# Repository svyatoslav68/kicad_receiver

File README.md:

Схема и печатная плата для FM-радиоприемника.

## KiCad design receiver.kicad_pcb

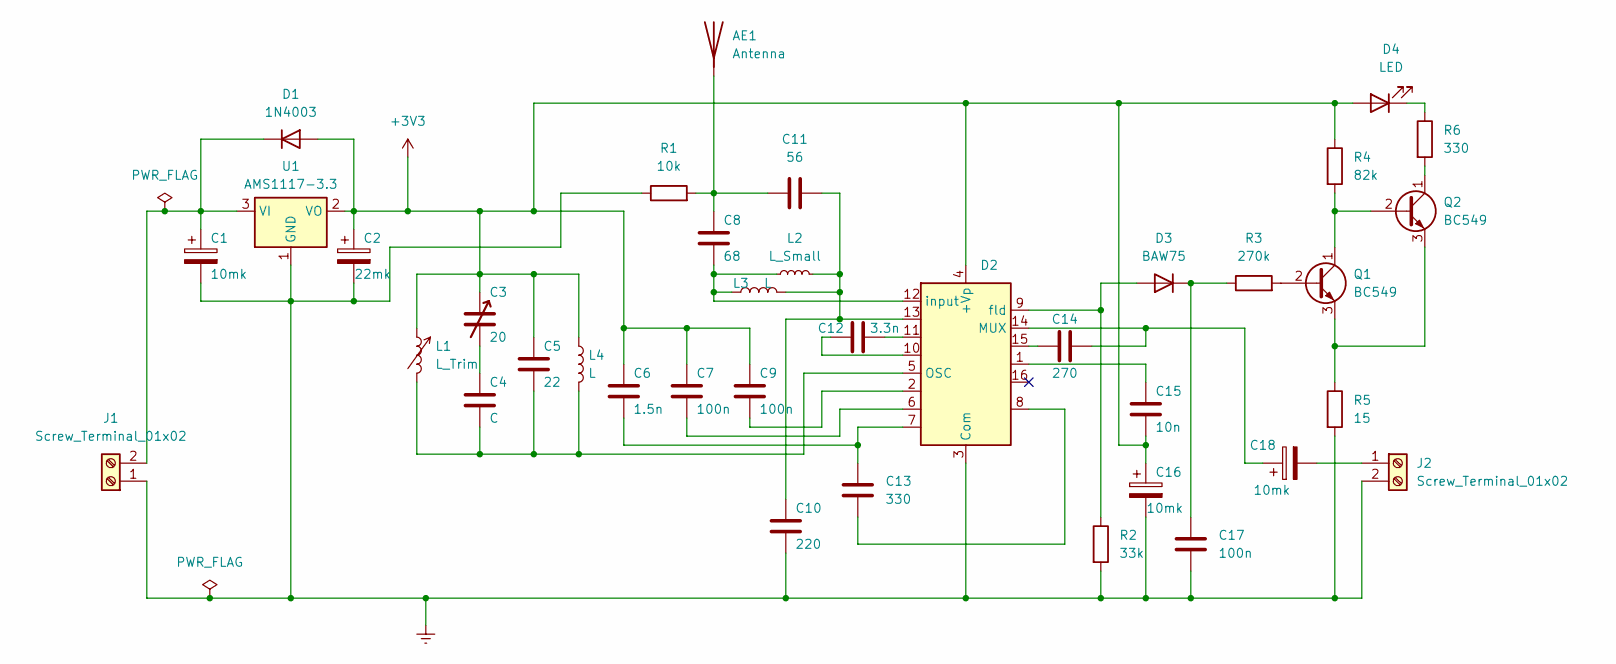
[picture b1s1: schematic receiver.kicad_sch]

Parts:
AE1: Antenna; Pin_D1.3mm_L11.3mm_W2.8mm_Flat
C1, C16, C18: 10mk; CP_Radial_D5.0mm_P2.00mm
C2: 22mk; C_Radial_D6.3mm_H5.0mm_P2.50mm
C3: 20; Capasitor_Variable
C4: C; C_Rect_L11.0mm_W2.8mm_P10.00mm_MKT
C5: 22; C_Rect_L11.0mm_W2.8mm_P10.00mm_MKT
C6: 1.5n; C_Rect_L4.0mm_W2.5mm_P2.50mm
C7, C9, C17: 100n; C_Axial_L5.1mm_D3.1mm_P15.00mm_Horizontal
C8: 68; C_Rect_L11.0mm_W2.8mm_P10.00mm_MKT
C10: 220; C_Rect_L4.6mm_W2.0mm_P2.50mm_MKS02_FKP02
C11: 56; C_Rect_L11.0mm_W2.8mm_P10.00mm_MKT
C12: 3.3n; C_Rect_L11.0mm_W2.8mm_P10.00mm_MKT
C13: 330; C_Rect_L9.0mm_W2.5mm_P7.50mm_MKT
C14: 270; C_Rect_L10.0mm_W2.5mm_P7.50mm_MKS4
C15: 10n; C_1206_3216Metric_Pad1.33x1.80mm_HandSolder
D1: 1N4003; D_DO-41_SOD81_P10.16mm_Horizontal
D2: SO-16_3.9x9.9mm_P1.27mm
D3: BAW75; D_DO-35_SOD27_P7.62mm_Horizontal
D4: LED; LED_D3.0mm
J1, J2: Screw_Terminal_01x02; Altech_AK300_1x02_P5.00mm_45-Degree
L1: L_Trim; L_Radial_L10.2mm_W10.2mm_Px7.62mm_Py7.62mm_Pulse_LP-30
L2: L_Small; L_Radial_L10.2mm_W10.2mm_Px7.62mm_Py7.62mm_Pulse_LP-30
L3, L4: L; L_1206_3216Metric_Pad1.22x1.90mm_HandSolder
Q1, Q2: BC549; TO-92_Inline
R1: 10k; R_1206_3216Metric_Pad1.30x1.75mm_HandSolder
R2: 33k; R_1206_3216Metric_Pad1.30x1.75mm_HandSolder
R3: 270k; R_1206_3216Metric_Pad1.30x1.75mm_HandSolder
R4: 82k; R_1206_3216Metric_Pad1.30x1.75mm_HandSolder
R5: 15; R_1206_3216Metric_Pad1.30x1.75mm_HandSolder
R6: 330; R_1206_3216Metric_Pad1.30x1.75mm_HandSolder
U1: AMS1117-3.3; SOT-223-3_TabPin2

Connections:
+3V3: C2.1, C3.1, C5.1, C6.1, C7.1, C9.1, C15.2, C16.1, D1.2 (A), D2.4 (+Vp), D4.2 (A), L1.1, L4.1, R4.1, U1.2 (VO)
Earth: C1.2, C2.2, C10.2, C16.2, C17.2, D2.3 (Com), J1.1, J2.2, R1.1, R2.2, R5.2, U1.1 (GND)
unnamed: AE1.1 (A), C8.1, C11.1, R1.2
unnamed: C3.2, C4.1
unnamed: C7.2, D2.6
unnamed: C9.2, D2.2
unnamed: C10.1, C11.2, D2.13, L2.2, L3.2
unnamed: C12.1, D2.10
unnamed: C12.2, D2.11
unnamed: C6.2, C13.1, D2.7
unnamed: C13.2, D2.8
unnamed: C14.1, D2.15
unnamed: C15.1, D2.1
unnamed: C1.1, D1.1 (K), J1.2, U1.3 (VI)
unnamed: C14.2, C18.1, D2.14 (MUX)
unnamed: C4.2, C5.2, D2.5 (OSC), L1.2, L4.2
unnamed: D2.9 (fld), D3.2 (A), R2.1
unnamed: C8.2, D2.12 (input), L2.1, L3.1
unnamed: C17.1, D3.1 (K), R3.1
unnamed: D4.1 (K), R6.1
unnamed: C18.2, J2.1
unnamed: Q1.2 (B), R3.2
unnamed: Q1.1 (C), Q2.2 (B), R4.2
unnamed: Q1.3 (E), Q2.3 (E), R5.1
unnamed: Q2.1 (C), R6.2

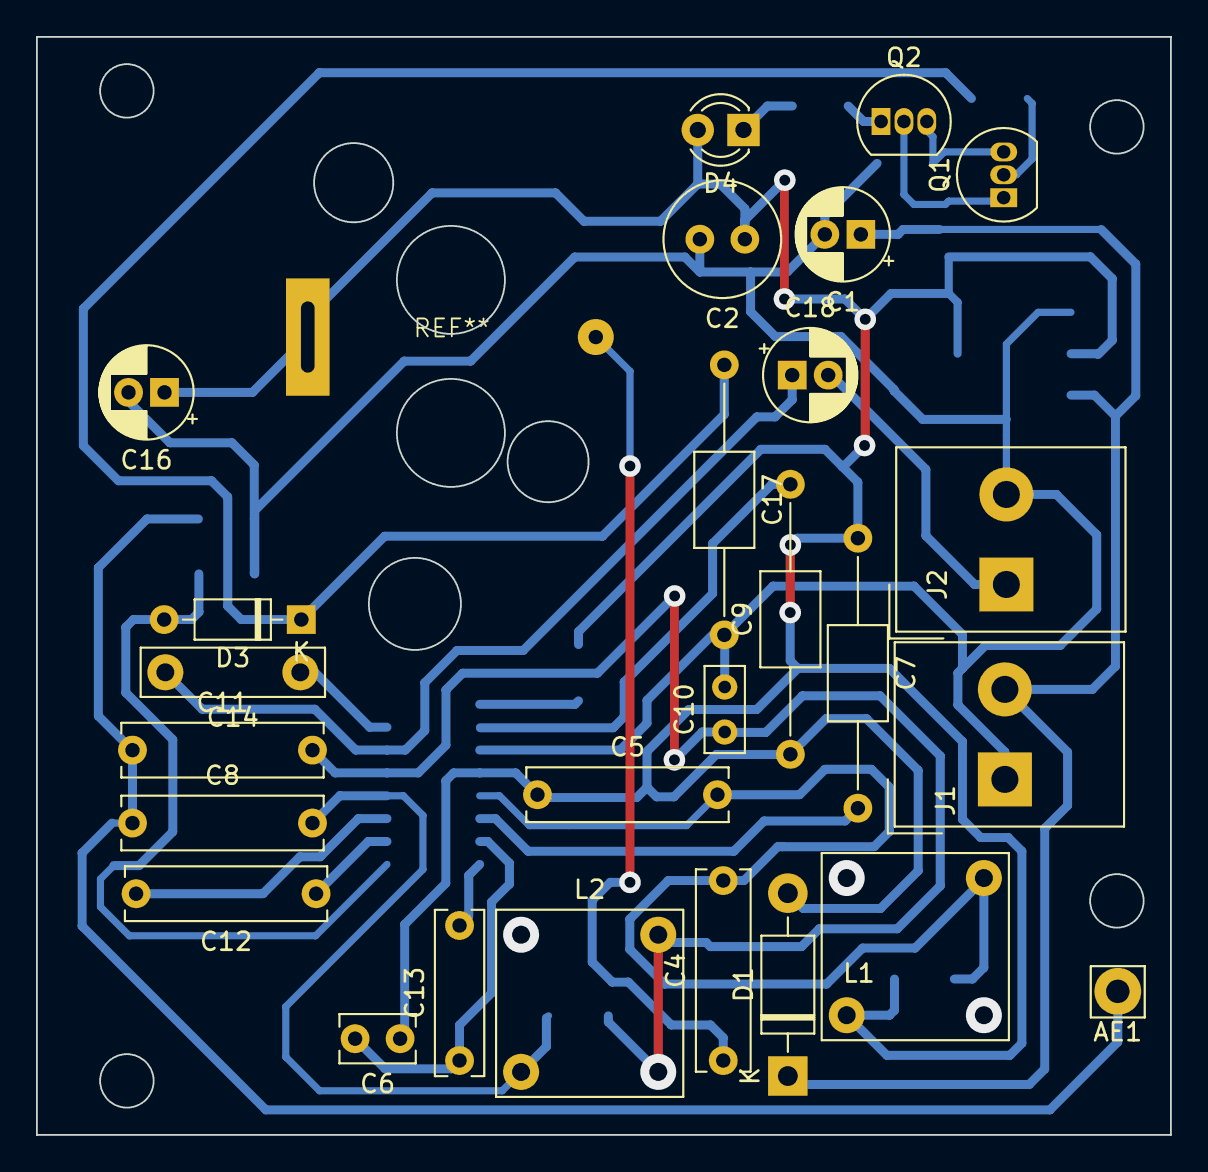
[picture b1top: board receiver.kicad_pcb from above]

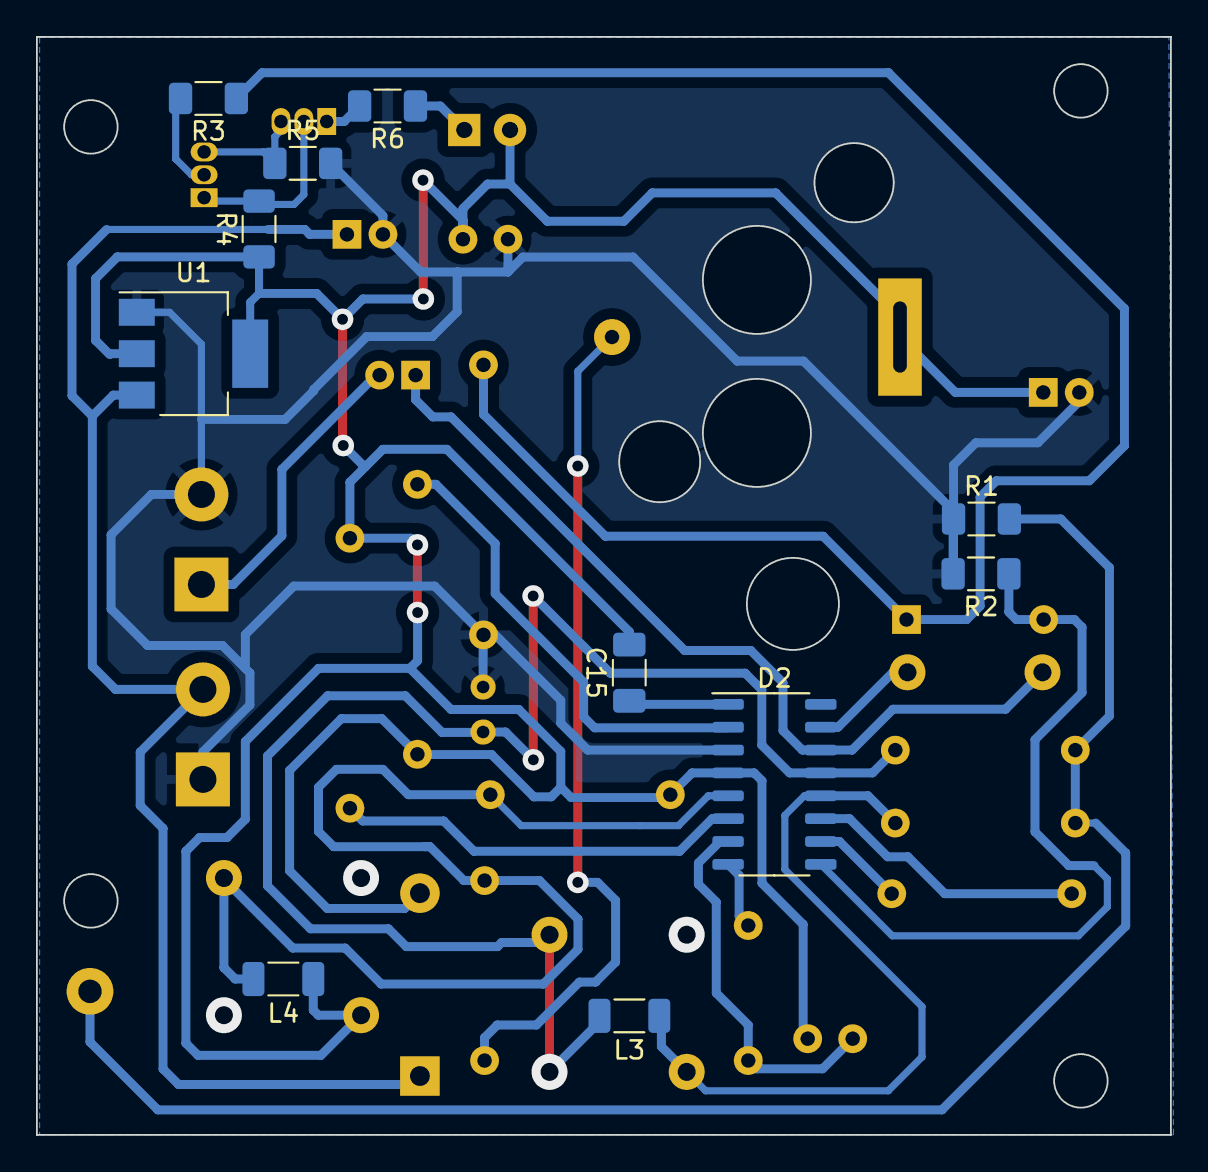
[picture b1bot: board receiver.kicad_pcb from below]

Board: 2 copper layers, 63.0 x 61.0 mm, 37 parts (11 on the bottom side), 24 nets.

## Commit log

2023-06-28 Sch worked
2023-07-01 Почти готово. Осталось добавить переменный конденсатор
2023-07-02 Почти все. Четыре дорожки внутри микросхемы. Это много.
2023-07-02 Уменьшена плотность дорожек
2023-07-03 Теперь только три дорожки между ножками микросхемы.
2023-07-03 Добавлена SMD-индуктивность.
2023-07-04 Добавлено посадочное место для переменного конденсатора.
2023-07-06 посадочные места катушек индуктивности размещены по местам. вроде бы,все готово к производству.
2023-07-06 немного отодвинул дорохки от отверстий крепления и утолщил дорожки.
2023-07-06 Создан pdf-документ с шестью риснуками платы.
